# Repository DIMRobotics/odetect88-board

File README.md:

odetect88-board
===============

Opponent detector board based on ATmega32U4

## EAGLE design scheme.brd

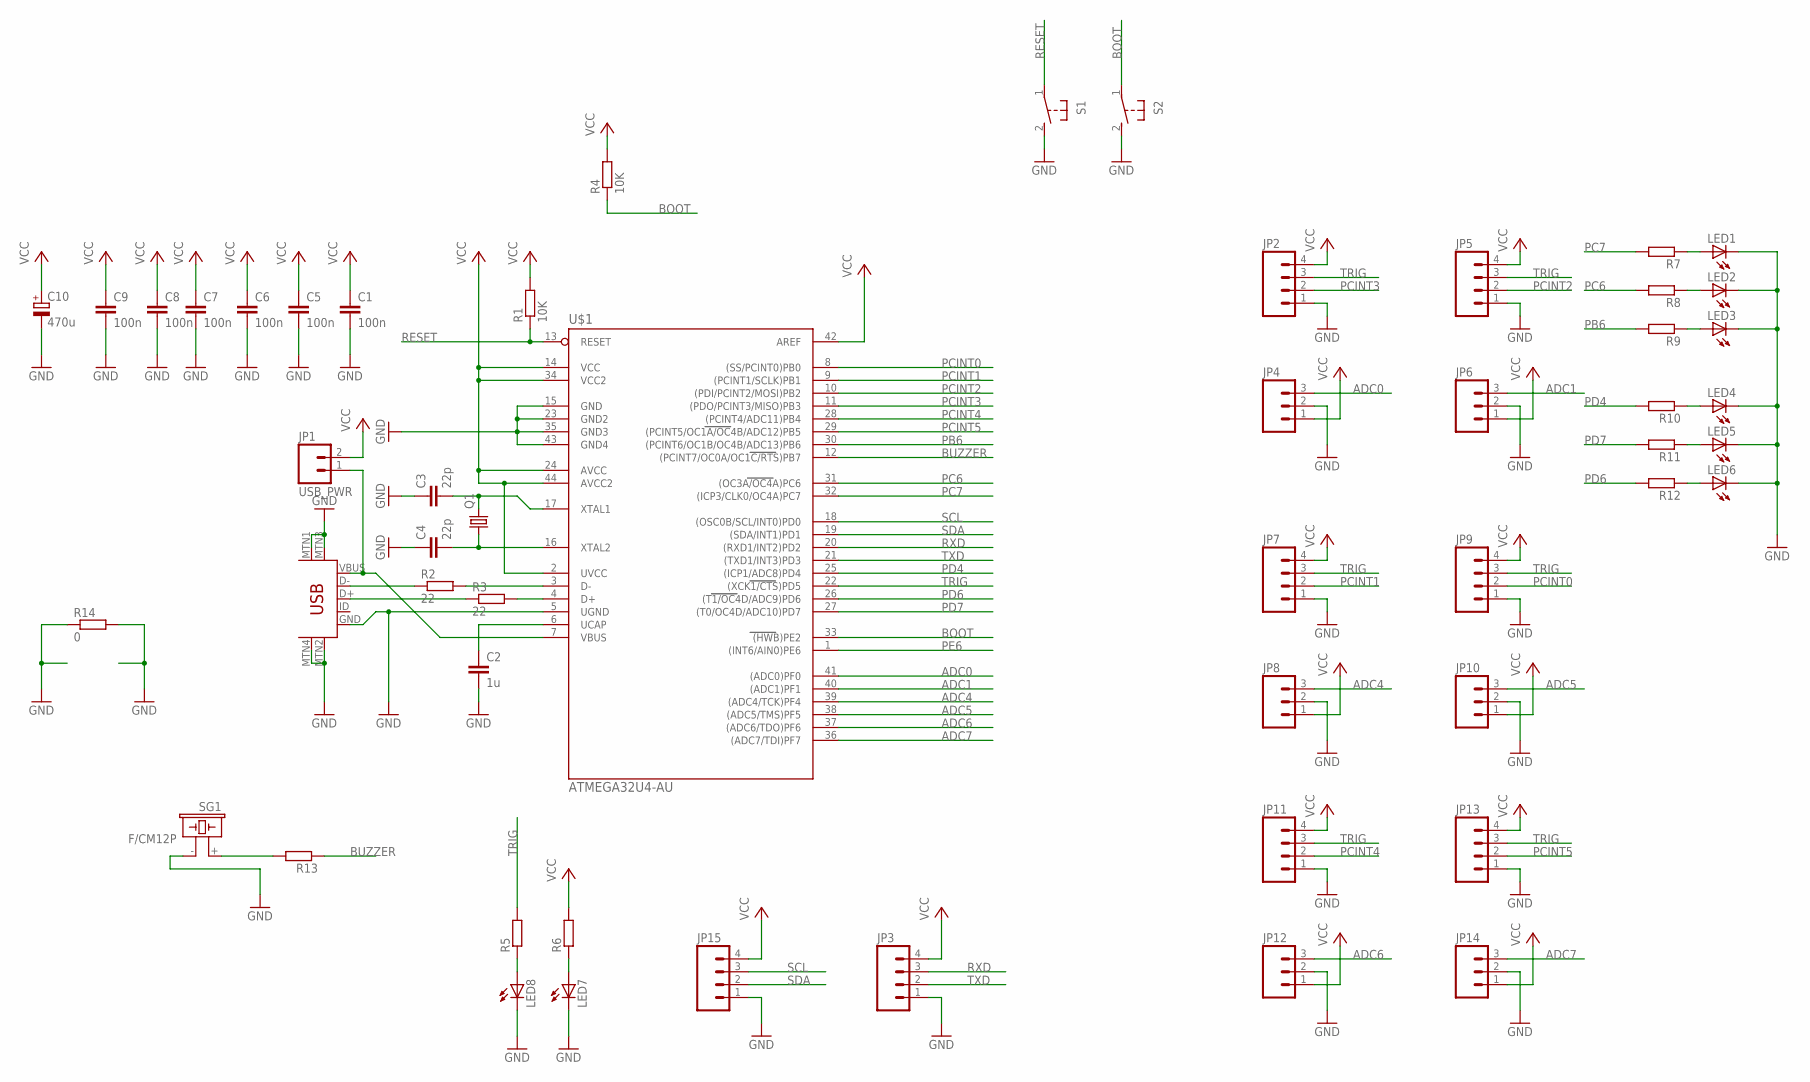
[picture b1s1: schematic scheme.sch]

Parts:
C1, C5, C6, C7, C8, C9: 100n; C0805
C2: 1u; C0805
C3, C4: 22p; C0805
C10: 470u; E3,5-8
JP1: USB_PWR; 1X02
JP2, JP3, JP5, JP7, JP9, JP11, JP13, JP15: M04PTH; 1X04
JP4, JP6, JP8, JP10, JP12, JP14: M03PTH; 1X03
LED1, LED2, LED3, LED4, LED5, LED6, LED7, LED8: LEDSMT1206; 1206
Q1: CRYSTALHC49S; HC49/S
R1, R4: 10K; R0805
R2, R3: 22; R0805
R5, R6, R7, R8, R9, R10, R11, R12, R13: R-EU_M0805; M0805
R14: 0; M1206
S1, S2: 31-XX; B3F-31XX
SG1: F/CM12P
U$1: ATMEGA32U4-AU; TQFP44
U$2: USB-MINIB-5PIN; USB-MINIB

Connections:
ADC0: JP4.3, U$1.41 ((ADC0)PF0)
ADC1: JP6.3, U$1.40 ((ADC1)PF1)
ADC4: JP8.3, U$1.39 ((ADC4/TCK)PF4)
ADC5: JP10.3, U$1.38 ((ADC5/TMS)PF5)
ADC6: JP12.3, U$1.37 ((ADC6/TDO)PF6)
ADC7: JP14.3, U$1.36 ((ADC7/TDI)PF7)
BOOT: R4.1, S2.1, U$1.33 ((HWB)PE2)
BUZZER: R13.1, U$1.12 ((PCINT7/OC0A/OC1C/RTS)PB7)
GND: C1.2, C2.2, C3.1, C4.1, C5.2, C6.2, C7.2, C8.2, C9.2, C10.-, JP2.1, JP3.1, JP4.2, JP5.1, JP6.2, JP7.1, JP8.2, JP9.1, JP10.2, JP11.1, JP12.2, JP13.1, JP14.2, JP15.1, LED1.C, LED2.C, LED3.C, LED4.C, LED5.C, LED6.C, LED7.C, LED8.C, R14.1, R14.2, S1.2 (S), S2.2 (S), SG1.- (2), U$1.5 (UGND), U$1.15 (GND), U$1.23 (GND2), U$1.35 (GND3), U$1.43 (GND4), U$2.GND, U$2.MTN1 (MTN2), U$2.MTN2 (MTN3), U$2.MTN3 (MTN1), U$2.MTN4
unnamed: JP1.1, U$1.7 (VBUS), U$2.VBUS
unnamed: R2.1, U$2.D-
unnamed: R2.2, U$1.3 (D-)
unnamed: R3.2, U$1.4 (D+)
unnamed: R3.1, U$2.D+
unnamed: C2.1, U$1.6 (UCAP)
unnamed: C4.2, Q1.1, U$1.16 (XTAL2)
unnamed: C3.2, Q1.2, U$1.17 (XTAL1)
unnamed: LED1.A, R7.1
unnamed: LED2.A, R8.1
unnamed: LED3.A, R9.1
unnamed: LED4.A, R10.1
unnamed: LED5.A, R11.1
unnamed: LED6.A, R12.1
unnamed: R13.2, SG1.+ (1)
unnamed: LED8.A, R5.1
unnamed: LED7.A, R6.1
PB6: R9.2, U$1.30 ((PCINT6/OC1B/OC4B/ADC13)PB6)
PC6: R8.2, U$1.31 ((OC3A/OC4A)PC6)
PC7: R7.2, U$1.32 ((ICP3/CLK0/OC4A)PC7)
PCINT0: JP9.2, U$1.8 ((SS/PCINT0)PB0)
PCINT1: JP7.2, U$1.9 ((PCINT1/SCLK)PB1)
PCINT2: JP5.2, U$1.10 ((PDI/PCINT2/MOSI)PB2)
PCINT3: JP2.2, U$1.11 ((PDO/PCINT3/MISO)PB3)
PCINT4: JP11.2, U$1.28 ((PCINT4/ADC11)PB4)
PCINT5: JP13.2, U$1.29 ((PCINT5/OC1A/OC4B/ADC12)PB5)
PD4: R10.2, U$1.25 ((ICP1/ADC8)PD4)
PD6: R12.2, U$1.26 ((T1/OC4D/ADC9)PD6)
PD7: R11.2, U$1.27 ((T0/OC4D/ADC10)PD7)
PE6: U$1.1 ((INT6/AIN0)PE6)
RESET: R1.1, S1.1, U$1.13 (RESET)
RXD: JP3.3, U$1.20 ((RXD1/INT2)PD2)
SCL: JP15.3, U$1.18 ((OSC0B/SCL/INT0)PD0)
SDA: JP15.2, U$1.19 ((SDA/INT1)PD1)
TRIG: JP2.3, JP5.3, JP7.3, JP9.3, JP11.3, JP13.3, R5.2, U$1.22 ((XCK1/CTS)PD5)
TXD: JP3.2, U$1.21 ((TXD1/INT3)PD3)
VCC: C1.1, C5.1, C6.1, C7.1, C8.1, C9.1, C10.+, JP1.2, JP2.4, JP3.4, JP4.1, JP5.4, JP6.1, JP7.4, JP8.1, JP9.4, JP10.1, JP11.4, JP12.1, JP13.4, JP14.1, JP15.4, R1.2, R4.2, R6.2, U$1.2 (UVCC), U$1.14 (VCC), U$1.24 (AVCC), U$1.34 (VCC2), U$1.42 (AREF), U$1.44 (AVCC2)

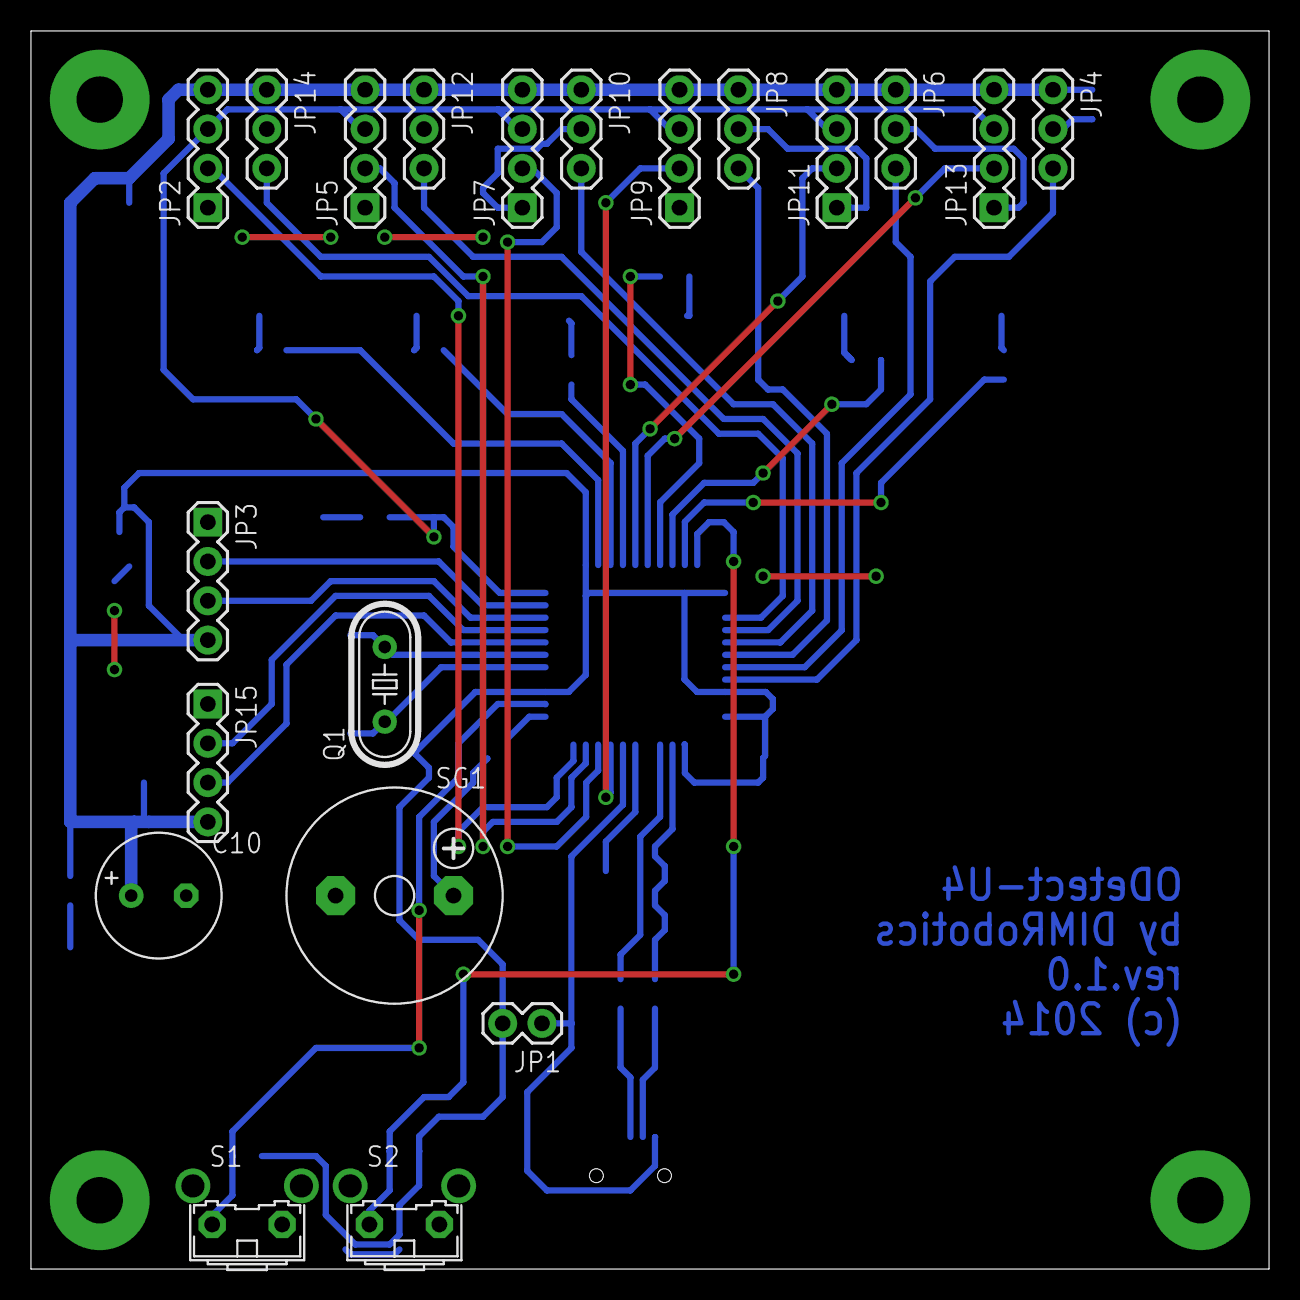
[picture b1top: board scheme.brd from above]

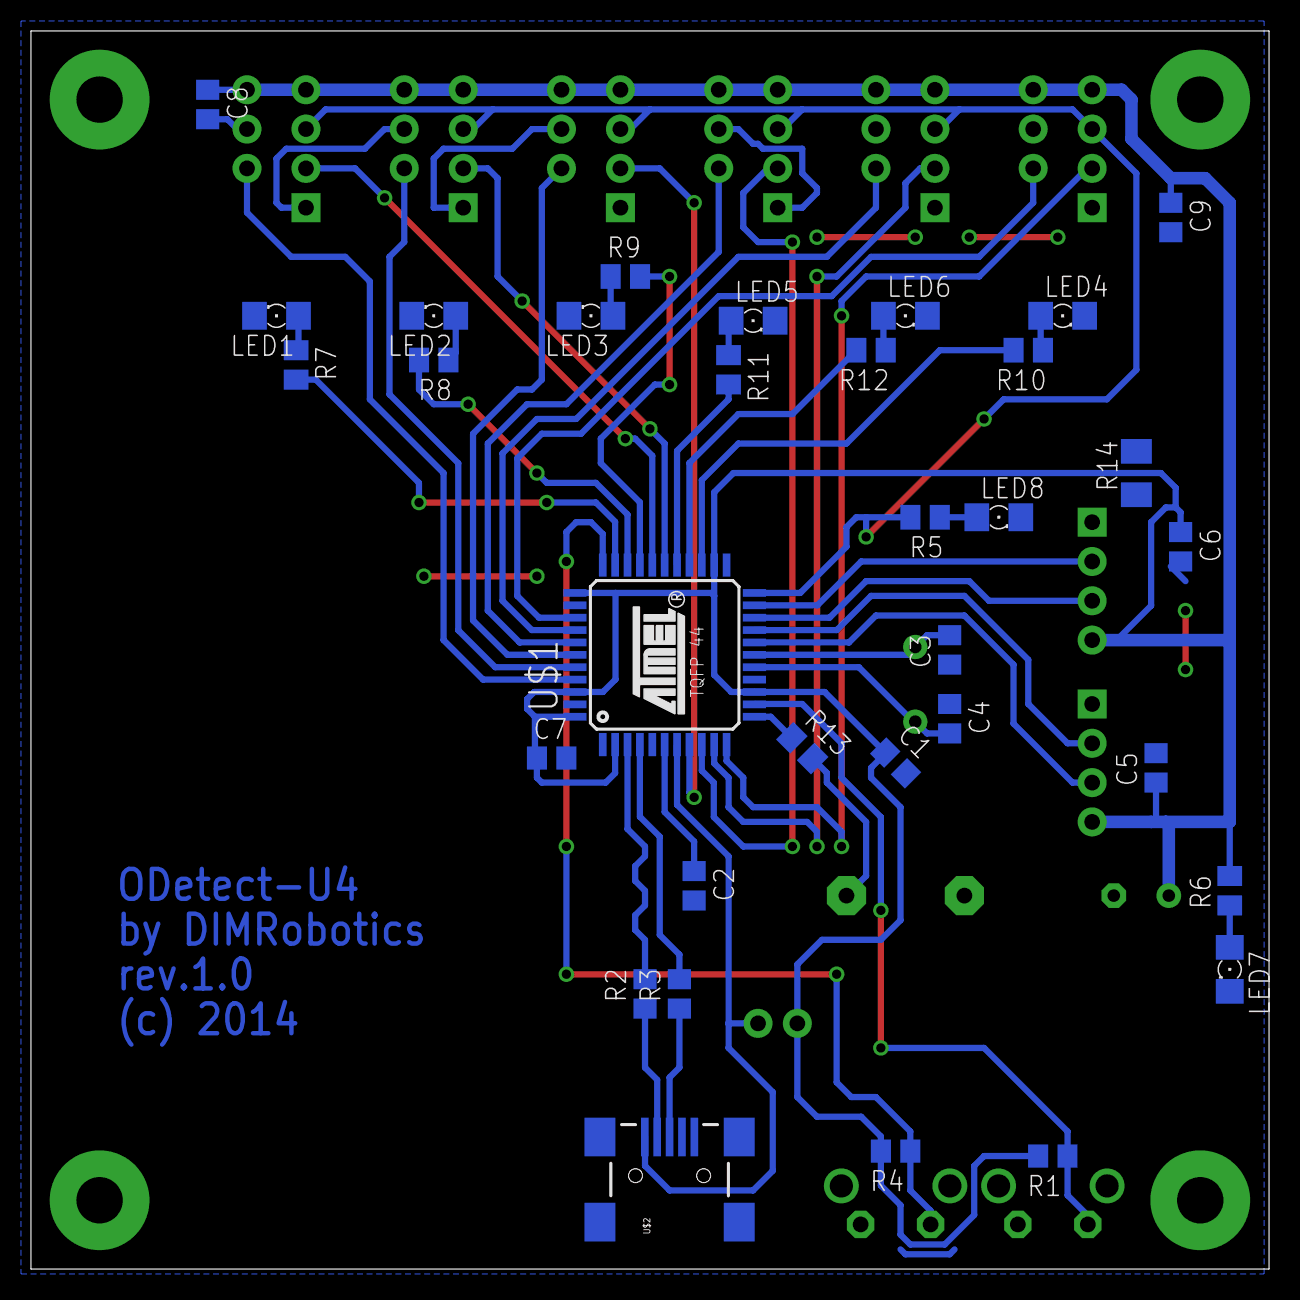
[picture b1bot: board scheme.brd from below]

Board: 2 copper layers, 80.0 x 80.0 mm, 53 parts (33 on the bottom side), 45 nets.

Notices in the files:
scheme.brd:
(c) 2014
parts and their libraries:
SparkFun-Connectors: Licensing: CC v3.0 Share-Alike You are welcome to use this library for commercial purposes.
